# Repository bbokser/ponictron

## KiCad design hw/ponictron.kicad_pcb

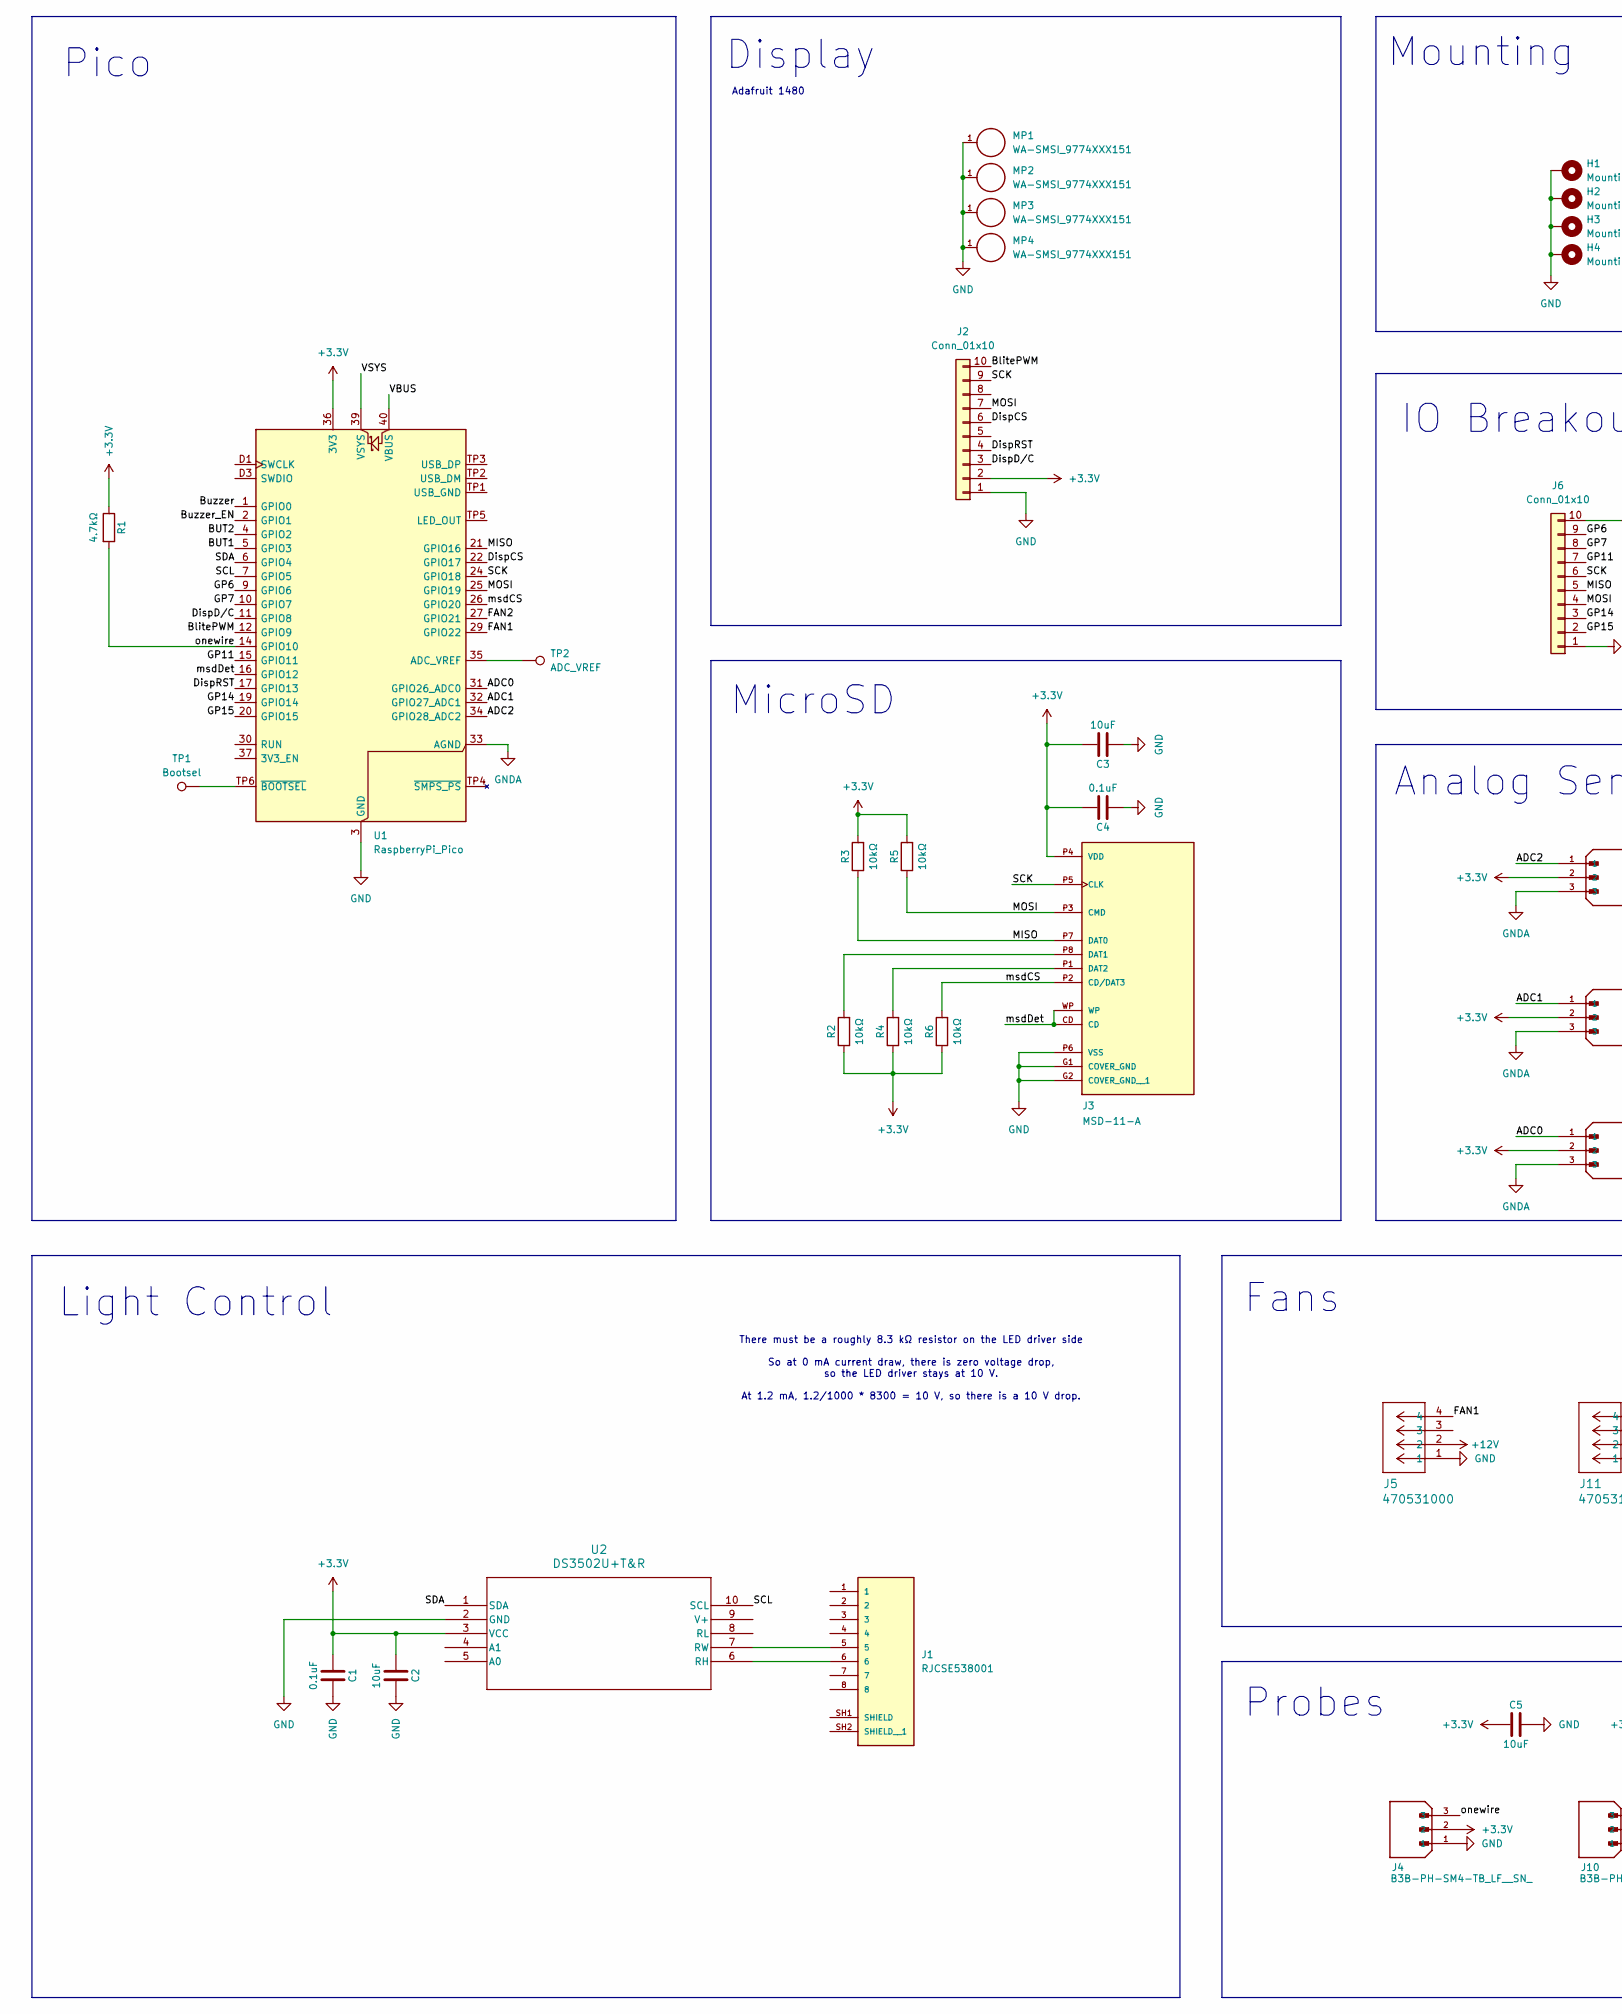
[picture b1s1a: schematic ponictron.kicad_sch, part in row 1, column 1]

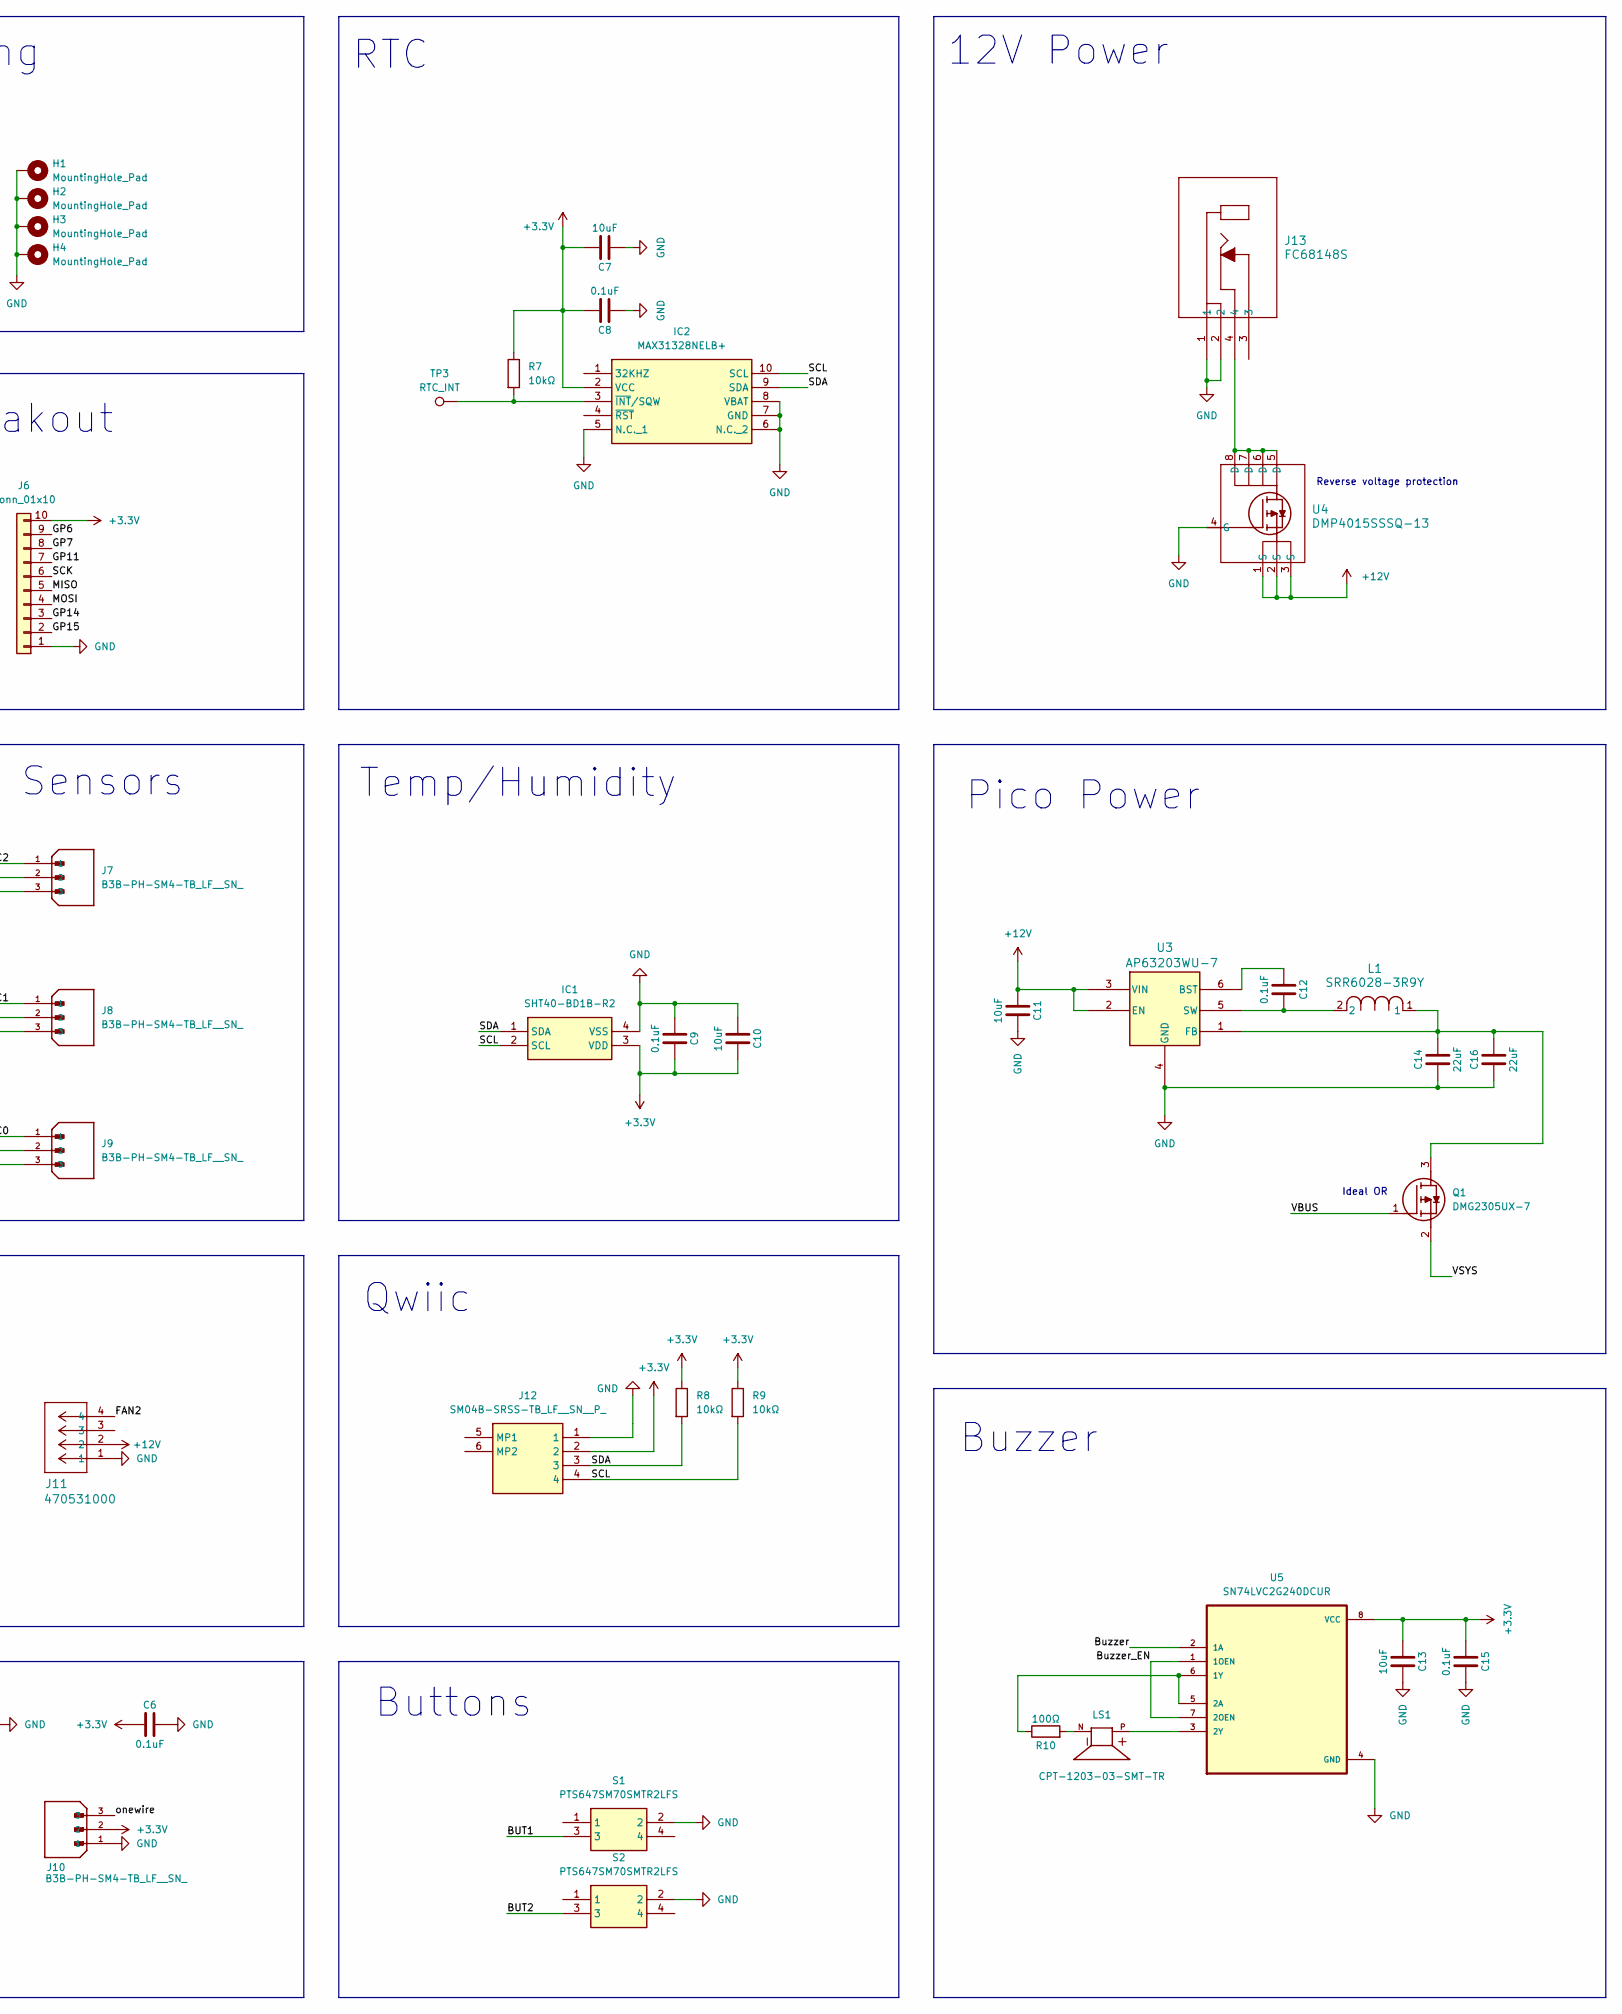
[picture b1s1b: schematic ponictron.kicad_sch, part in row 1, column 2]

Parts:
C1, C4, C6, C8, C9, C12, C15: 0.1uF; C_0603_1608Metric; LCSC Part # C105524
C2, C3, C5, C7, C10, C11, C13: 10uF; C_0603_1608Metric; LCSC Part # C105524
C14, C16: 22uF; C_0603_1608Metric; LCSC Part # C105524
H1, H2, H3, H4: MountingHole_Pad; MountingHole_2.7mm_M2.5_DIN965_Pad
IC1: SHT40-BD1B-R2; SHT40BD1BR2; Mouser Part Number 403-SHT40-BD1B-R2
IC2: MAX31328NELB+; MAX31328NELB; Mouser Part Number 700-MAX31328NELB+
J1: RJCSE538001; AMPHENOL_RJCSE538001; PARTREV A
J2, J6: Conn_01x10; PinSocket_1x10_P2.54mm_Vertical
J3: MSD-11-A; CUI_MSD-11-A; PARTREV 1.02
J4, J7, J8, J9, J10: B3B-PH-SM4-TB_LF__SN_; JST_B3B-PH-SM4-TB_LF__SN_; PARTREV N/A
J5, J11: 470531000; CONN_SD-47053-001_H10p00_MOL
J12: SM04B-SRSS-TB_LF__SN__P_; SM04BSRSSTBLFSNP; Mouser Part Number 306-SM04BSRSSTBLFSNP
J13: FC68148S; FC68148S_CLF
L1: SRR6028-3R9Y; IND_BOURNS_SRR6028
LS1: CPT-1203-03-SMT-TR; XDCR_CPT-1203-03-SMT-TR; PARTREV 1.0
MP1, MP2, MP3, MP4: WA-SMSI_9774XXX151; WA-SMSI_9774100151; PART-NUMBER 9774100151R
Q1: DMG2305UX-7; SOT96P240X115-3N; Mouser Part Number 621-DMG2305UX-7
R1: 4.7kΩ; R_0603_1608Metric_Pad0.98x0.95mm_HandSolder; LCSC Part # C15401
R2, R3, R4, R5, R6, R7, R8, R9: 10kΩ; R_0603_1608Metric_Pad0.98x0.95mm_HandSolder; LCSC Part # C15401
R10: 100Ω; R_0603_1608Metric_Pad0.98x0.95mm_HandSolder; LCSC Part # C15401
S1, S2: PTS647SM70SMTR2LFS; PTS647SM38SMTR2LFS; Mouser Part Number 611-PTS647SM70SMTR2L
TP1: Bootsel; TestPoint_Pad_1.5x1.5mm
TP2: ADC_VREF; TestPoint_Pad_1.5x1.5mm
TP3: RTC_INT; TestPoint_Pad_1.5x1.5mm
U1: RaspberryPi_Pico; RaspberryPi_Pico_Original_SMD
U2: DS3502U+T&R; DS3502U_T_R-L
U3: AP63203WU-7; AP63203WU-7_DIO-L
U4: DMP4015SSSQ-13; SO8_DIO
U5: SN74LVC2G240DCUR

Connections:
+3.3V: C1.2, C2.2, C3.1, C4.1, C5.2, C6.2, C7.1, C8.1, C9.1, C10.1, C13.2, C15.2, IC1.3 (VDD), IC2.2 (VCC), J2.2, J3.P4 (VDD), J4.2, J6.10, J7.2, J8.2, J9.2, J10.2, J12.2, R1.1, R2.1, R3.2, R4.1, R5.2, R6.1, R7.1, R8.1, R9.1, U1.36 (3V3), U2.3 (VCC), U5.8 (VCC)
+12V: C11.2, J5.2, J11.2, U3.2 (EN), U3.3 (VIN), U4.1 (S), U4.2 (S), U4.3 (S)
/ADC0: J9.1, U1.31 (GPIO26_ADC0)
/ADC1: J8.1, U1.32 (GPIO27_ADC1)
/ADC2: J7.1, U1.34 (GPIO28_ADC2)
/BUT1: S1.3, U1.5 (GPIO3)
/BUT2: S2.3, U1.4 (GPIO2)
/BlitePWM: J2.10, U1.12 (GPIO9)
/Buzzer: U1.1 (GPIO0), U5.2 (1A)
/Buzzer_EN: U1.2 (GPIO1), U5.1 (1OEN), U5.7 (2OEN)
/DispCS: J2.6, U1.22 (GPIO17)
/DispD/C: J2.3, U1.11 (GPIO8)
/DispRST: J2.4, U1.17 (GPIO13)
/FAN1: J5.4, U1.29 (GPIO22)
/FAN2: J11.4, U1.27 (GPIO21)
/GP6: J6.9, U1.9 (GPIO6)
/GP7: J6.8, U1.10 (GPIO7)
/GP11: J6.7, U1.15 (GPIO11)
/GP14: J6.3, U1.19 (GPIO14)
/GP15: J6.2, U1.20 (GPIO15)
/MISO: J3.P7 (DAT0), J6.5, R3.1, U1.21 (GPIO16)
/MOSI: J2.7, J3.P3 (CMD), J6.4, R5.1, U1.25 (GPIO19)
/SCK: J2.9, J3.P5 (CLK), J6.6, U1.24 (GPIO18)
/SCL: IC1.2 (SCL), IC2.10 (SCL), J12.4, R9.2, U1.7 (GPIO5), U2.10 (SCL)
/SDA: IC1.1 (SDA), IC2.9 (SDA), J12.3, R8.2, U1.6 (GPIO4), U2.1 (SDA)
/VBUS: Q1.1 (G), U1.40 (VBUS)
/VSYS: Q1.2 (S), U1.39 (VSYS)
/msdCS: J3.P2 (CD/DAT3), R6.2, U1.26 (GPIO20)
/msdDet: J3.CD, J3.WP, U1.16 (GPIO12)
/onewire: J4.3, J10.3, R1.2, U1.14 (GPIO10)
GND: C1.1, C2.1, C3.2, C4.2, C5.1, C6.1, C7.2, C8.2, C9.2, C10.2, C11.1, C13.1, C14.2, C15.1, C16.2, H1.1, H2.1, H3.1, H4.1, IC1.4 (VSS), IC2.5 (N.C._1), IC2.6 (N.C._2), IC2.7 (GND), IC2.8 (VBAT), J2.1, J3.G1 (COVER_GND), J3.G2 (COVER_GND__1), J3.P6 (VSS), J4.1, J5.1, J6.1, J10.1, J11.1, J12.1, J13.1, J13.2, MP1.1, MP2.1, MP3.1, MP4.1, S1.2, S2.2, U1.3 (GND), U1.8 (GND), U1.13 (GND), U1.18 (GND), U1.23 (GND), U1.28 (GND), U1.38 (GND), U1.D2 (GND), U2.2 (GND), U3.4 (GND), U4.4 (G), U5.4 (GND)
GNDA: J7.3, J8.3, J9.3, U1.33 (AGND)
unnamed: IC2.3 (~INT/SQW), R7.2, TP3.1
unnamed: J3.P8 (DAT1), R2.2
unnamed: J3.P1 (DAT2), R4.2
unnamed: J13.4, U4.5 (D), U4.6 (D), U4.7 (D), U4.8 (D)
unnamed: LS1.N, R10.2
unnamed: C14.1, C16.1, L1.1, Q1.3 (D), U3.1 (FB)
unnamed: TP2.1, U1.35 (ADC_VREF)
unnamed: TP1.1, U1.TP6 (~BOOTSEL)
unnamed: J1.6, U2.6 (RH)
unnamed: J1.5, U2.7 (RW)
unnamed: C12.2, U3.6 (BST)
unnamed: C12.1, L1.2, U3.5 (SW)
unnamed: R10.1, U5.5 (2A), U5.6 (1Y)
unnamed: LS1.P, U5.3 (2Y)

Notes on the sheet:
Buttons
Ideal OR
IO Breakout
MicroSD
Adafruit 1480
Fans
Mounting
Reverse voltage protection
Analog Sensors
RTC
Display
Buzzer
Probes
12V Power
Temp/Humidity
Qwiic
Light Control
Pico
Pico Power
There must be a roughly 8.3 kΩ resistor on the LED driver side So at 0 mA current draw, there is zero voltage drop, so the LED driver stays at 10 V. At 1.2 mA, 1.2/1000 * 8300 = 10 V, so there is a 10 V drop.

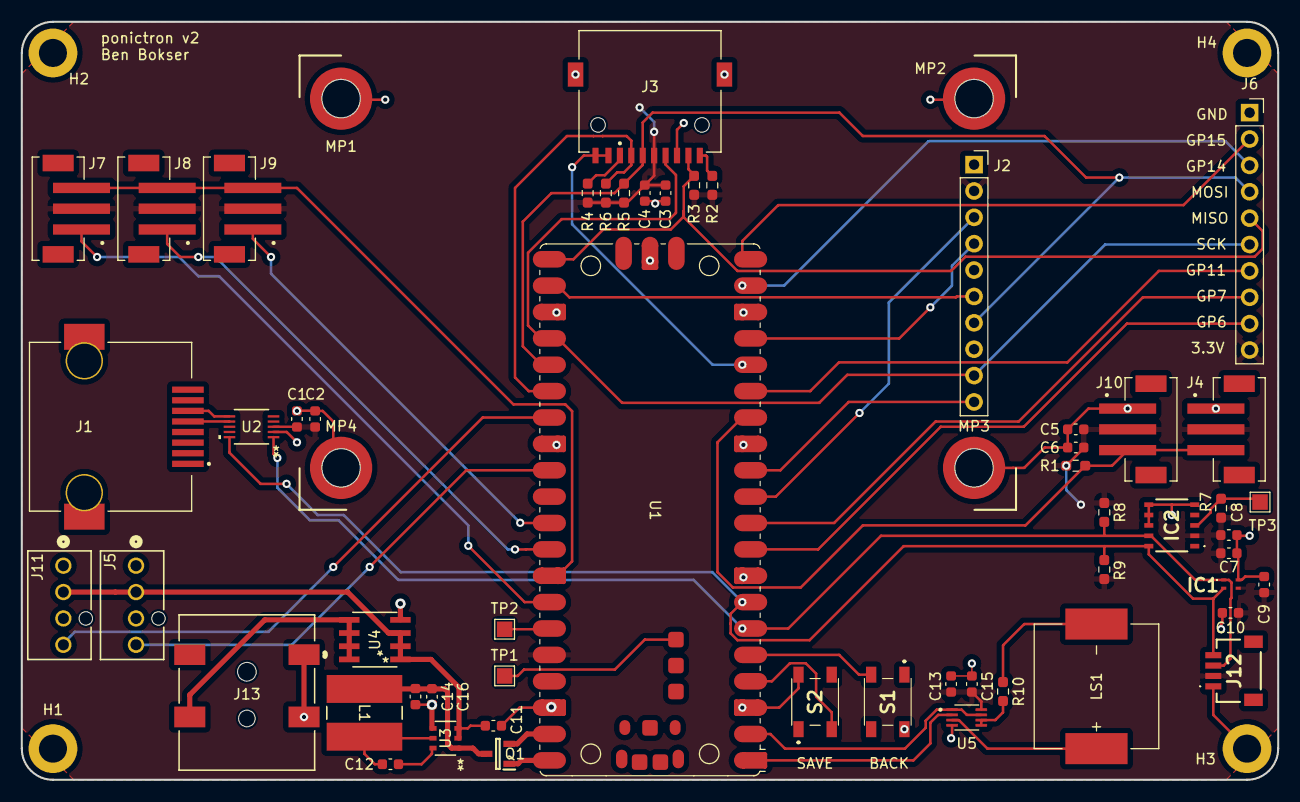
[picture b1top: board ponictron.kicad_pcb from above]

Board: 2 copper layers, 121.0 x 73.0 mm, 62 parts (0 on the bottom side), 46 nets.

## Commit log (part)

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2025-12-11 Initialize KiCAD project
2025-12-14 Working on power and light control circuits
2025-12-15 Finish light control and power circuits
2025-12-15 Further progress on schematic
2025-12-24 Add slider switch
2025-12-27 Further updates to schematic
2025-12-31 Add expander
2025-12-31 Remove expander, switch to TFT display, ready for board layout
2026-01-19 Starting board layout
2026-01-26 Create board layout
2026-02-15 Making changes to schematic based on feedback
2026-02-15 Fix trace widths, update 3D models
2026-02-16 Change display thru-holes to insert mounts
2026-04-04 Init firmware
2026-04-05 Fixing firmware bugs
2026-04-05 Get display nominally running
2026-04-16 Writing display and options functionality
2026-04-16 Fix several bugs
2026-04-20 Massive rewrite of disp and fsm for faster display
2026-04-21 Bugfixes
2026-06-13 Work around encoder issue using i2c encoder, fixing various issues
2026-06-14 Various improvements to GUI
2026-06-21 Add light options
2026-06-21 Fix various bugs, add brightness range
2026-06-27 Add idle state
2026-06-27 Add fan speed setting option
